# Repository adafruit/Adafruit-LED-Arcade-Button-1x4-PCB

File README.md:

## Adafruit LED Arcade Button 1x4 - STEMMA QT I2C Breakout PCB

<a href="http://www.adafruit.com/products/5296"><br/>
Click here to purchase one from the Adafruit shop</a>

PCB files for the Adafruit LED Arcade Button 1x4 - STEMMA QT I2C Breakout

Format is EagleCAD schematic and board layout
* https://www.adafruit.com/product/5296

### Description

The only thing better than a glowy arcade button is, perhaps, FOUR glowing arcade buttons - and that's what the Adafruit LED Arcade Button 1x4 QT I2C Breakout will let you do! This long 3" x 0.8" PCB has 8 x JST XH sockets that will fit our arcade button quick connects. Each XH pair lets you connect one arcade button that has a built in LED illuminator, and makes it easy to use with a breadboard/perfboard or with a STEMMA QT (Qwiic) connector for instant I2C connectivity on any platform.

### License

Adafruit invests time and resources providing this open source design, please support Adafruit and open-source hardware by purchasing products from [Adafruit](https://www.adafruit.com)!

Designed by Limor Fried/Ladyada for Adafruit Industries.

Creative Commons Attribution/Share-Alike, all text above must be included in any redistribution. 
See license.txt for additional details.

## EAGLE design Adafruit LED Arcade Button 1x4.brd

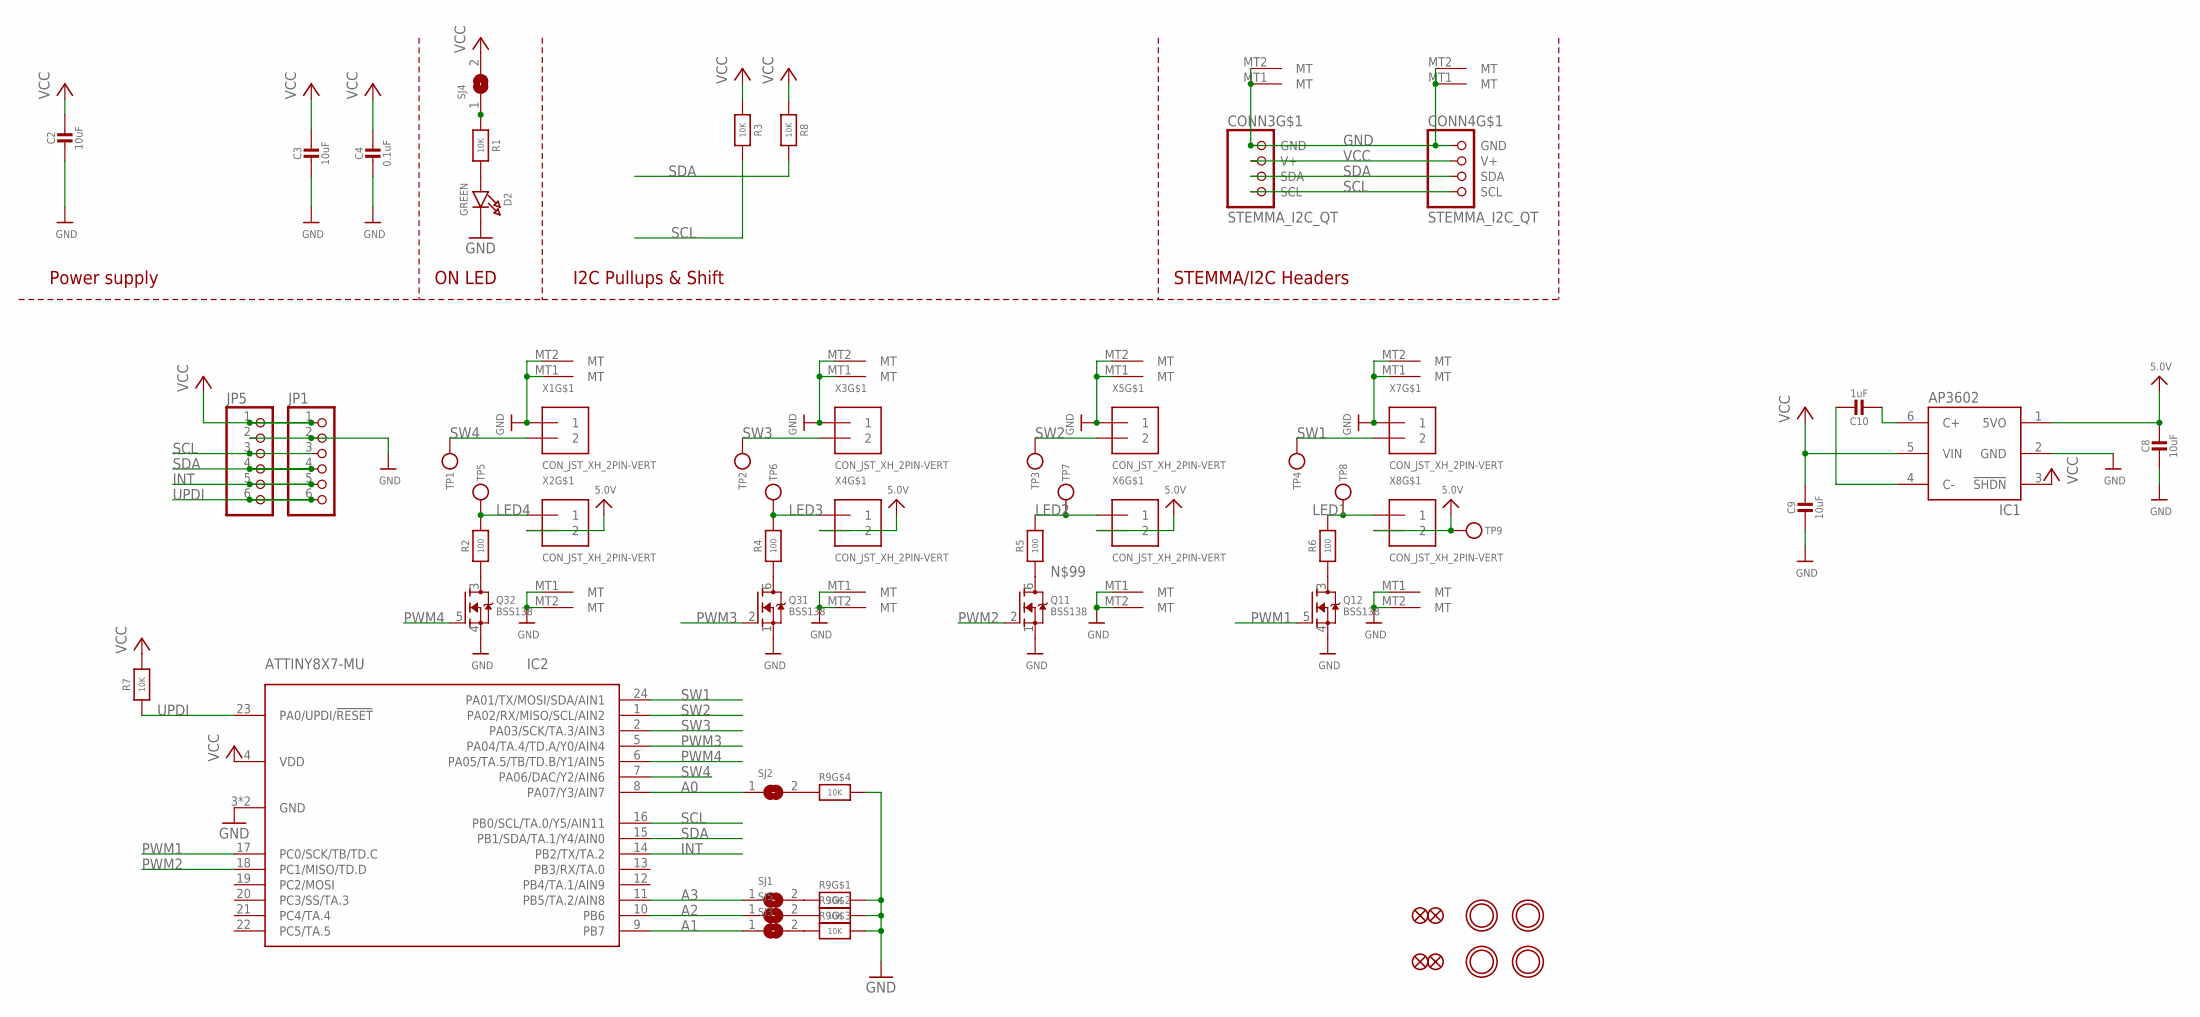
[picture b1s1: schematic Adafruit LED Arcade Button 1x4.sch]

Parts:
C2, C3, C8, C9: 10uF; 0805-NO
C4: 0.1uF; 0603-NO
C10: 1uF; 0805-NO
CONN3, CONN4: STEMMA_I2C_QT; JST_SH4
D2: GREEN; CHIPLED_0603_NOOUTLINE
FID1, FID2, FID3, FID4: FIDUCIAL_1MM
IC1: AP3602; SOT23-6
IC2: ATTINY8X7-MU; QFN24_4MM
JP1, JP5: HEADER-1X670MIL; 1X06_ROUND_70
Q1, Q3: BSS138; SOT363
R1, R3, R7, R8: 10K; 0603-NO
R2, R4, R5, R6: 100; 0603-NO
R9: 10K; RESPACK_4X0603
SJ1, SJ2, SJ3, SJ4, SJ5: SOLDERJUMPERCLOSED; SOLDERJUMPER_CLOSEDWIRE
TP1, TP2, TP3, TP4, TP5, TP6, TP7, TP8, TP9: TESTPOINTROUND1.5MM; TESTPOINT_ROUND_1.5MM
U$3, U$17, U$19, U$21: MOUNTINGHOLE2.5; MOUNTINGHOLE_2.5_PLATED
X1, X2, X3, X4, X5, X6, X7, X8: CON_JST_XH_2PIN-VERT; JST-XH-2-SV

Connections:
5.0V: C8.1, IC1.1 (5VO), TP9.P$1, X2.2, X4.2, X6.2, X8.2
A0: IC2.8 (PA07/Y3/AIN7), SJ2.1
A1: IC2.9 (PB7), SJ3.1
A2: IC2.10 (PB6), SJ5.1
A3: IC2.11 (PB5/TA.2/AIN8), SJ1.1
GND: C2.2, C3.2, C4.2, C8.2, C9.2, CONN3.1 (GND), CONN3.MT1 (MT), CONN3.MT2 (MT), CONN4.1 (GND), CONN4.MT1 (MT), CONN4.MT2 (MT), D2.C, IC1.2 (GND), IC2.3 (GND), IC2.THERM (GND), JP1.2, JP5.2, Q1.1 (S), Q1.4 (S), Q3.1 (S), Q3.4 (S), R9.5 (2), R9.6 (2), R9.7 (2), R9.8 (2), X1.1, X1.MT1 (MT), X1.MT2 (MT), X2.MT1 (MT), X2.MT2 (MT), X3.1, X3.MT1 (MT), X3.MT2 (MT), X4.MT1 (MT), X4.MT2 (MT), X5.1, X5.MT1 (MT), X5.MT2 (MT), X6.MT1 (MT), X6.MT2 (MT), X7.1, X7.MT1 (MT), X7.MT2 (MT), X8.MT1 (MT), X8.MT2 (MT)
INT: IC2.14 (PB2/TX/TA.2), JP1.5, JP5.5
LED1: R6.2, TP8.P$1, X8.1
LED2: R5.2, TP7.P$1, X6.1
LED3: R4.2, TP6.P$1, X4.1
LED4: R2.2, TP5.P$1, X2.1
unnamed: D2.A, R1.2
unnamed: C10.2, IC1.6 (C+)
unnamed: C10.1, IC1.4 (C-)
unnamed: Q3.6 (D), R4.1
unnamed: R1.1, SJ4.1
unnamed: R9.1, SJ1.2
unnamed: R9.2 (1), SJ5.2
unnamed: R9.3 (1), SJ3.2
unnamed: Q1.3 (D), R6.1
unnamed: Q3.3 (D), R2.1
unnamed: R9.4 (1), SJ2.2
unnamed: Q1.6 (D), R5.1
PWM1: IC2.17 (PC0/SCK/TB/TD.C), Q1.5 (G)
PWM2: IC2.18 (PC1/MISO/TD.D), Q1.2 (G)
PWM3: IC2.5 (PA04/TA.4/TD.A/Y0/AIN4), Q3.2 (G)
PWM4: IC2.6 (PA05/TA.5/TB/TD.B/Y1/AIN5), Q3.5 (G)
SCL: CONN3.4 (SCL), CONN4.4 (SCL), IC2.16 (PB0/SCL/TA.0/Y5/AIN11), JP1.3, JP5.3, R3.2
SDA: CONN3.3 (SDA), CONN4.3 (SDA), IC2.15 (PB1/SDA/TA.1/Y4/AIN0), JP1.4, JP5.4, R8.2
SW1: IC2.24 (PA01/TX/MOSI/SDA/AIN1), TP4.P$1, X7.2
SW2: IC2.1 (PA02/RX/MISO/SCL/AIN2), TP3.P$1, X5.2
SW3: IC2.2 (PA03/SCK/TA.3/AIN3), TP2.P$1, X3.2
SW4: IC2.7 (PA06/DAC/Y2/AIN6), TP1.P$1, X1.2
UPDI: IC2.23 (PA0/UPDI/!RESET), JP1.6, JP5.6, R7.1
VCC: C2.1, C3.1, C4.1, C9.1, CONN3.2 (V+), CONN4.2 (V+), IC1.3 (!SHDN), IC1.5 (VIN), IC2.4 (VDD), JP1.1, JP5.1, R3.1, R7.2, R8.1, SJ4.2

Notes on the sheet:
I2C Pullups & Shift
STEMMA/I2C Headers
ON LED
Power supply

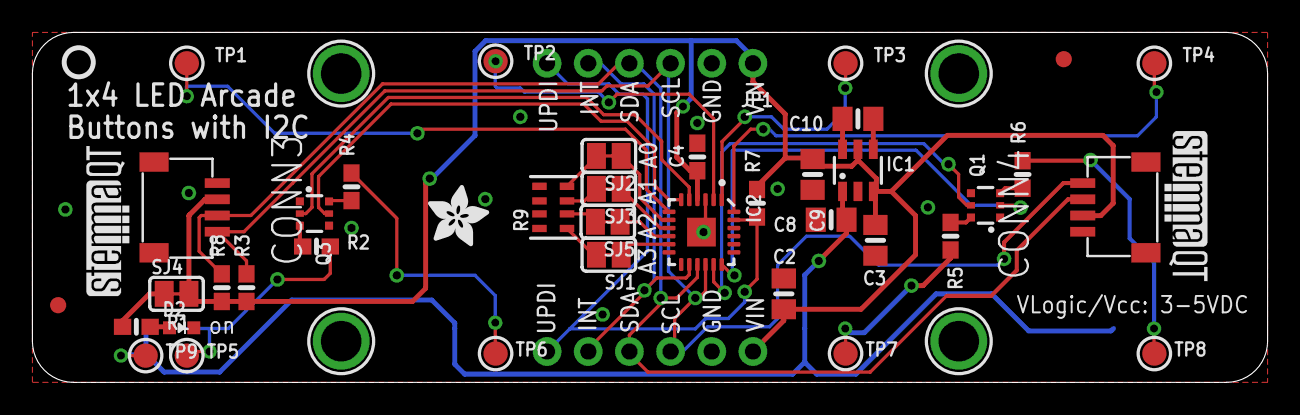
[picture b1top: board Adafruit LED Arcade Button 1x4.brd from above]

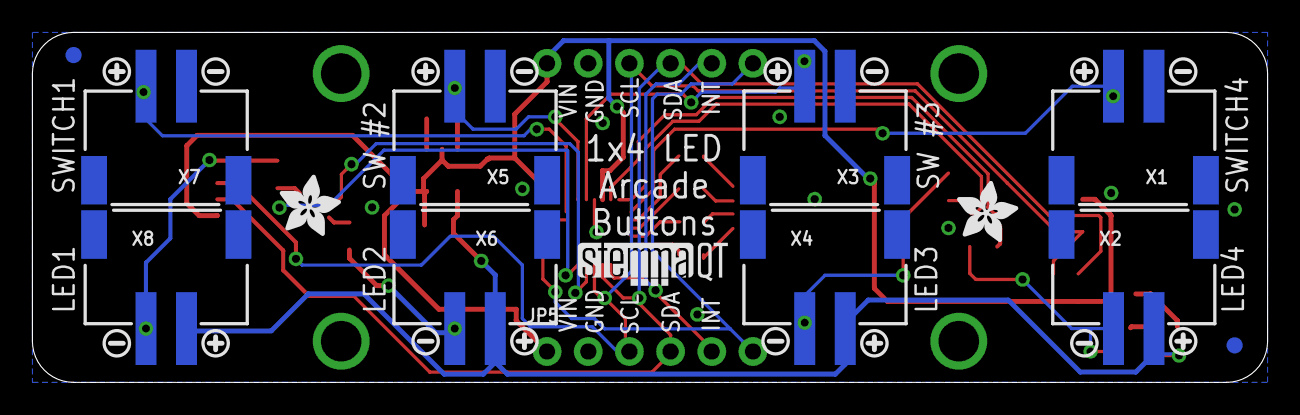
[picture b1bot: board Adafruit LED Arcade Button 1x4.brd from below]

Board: 2 copper layers, 76.2 x 21.6 mm, 77 parts (30 on the bottom side), 35 nets.

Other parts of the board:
U$1, U$8, U$14, U$45, U$46, U$47, U$48, U$49: SYMBOL_MINUS
U$2, U$9, U$52: ADAFRUIT_3.5MM
U$7, U$15, U$16, U$20, U$23, U$24, U$26, U$50: SYMBOL_PLUS
U$25: PCBFEAT-REV-040
U$30, U$31, U$53: STEMMAQT

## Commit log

2022-02-01 Initial commit, added files

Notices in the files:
parts and their libraries:
microbuilder: This work is placed in the public domain, and may be freely used for commercial and non-commercial work with the following conditions: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
